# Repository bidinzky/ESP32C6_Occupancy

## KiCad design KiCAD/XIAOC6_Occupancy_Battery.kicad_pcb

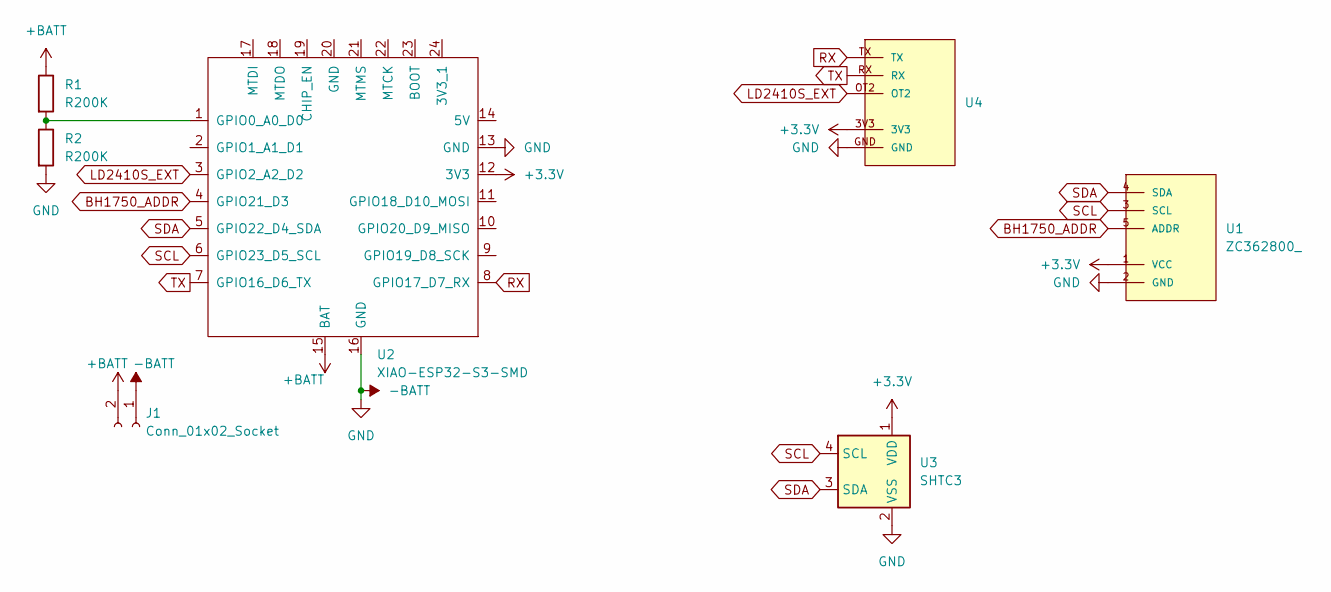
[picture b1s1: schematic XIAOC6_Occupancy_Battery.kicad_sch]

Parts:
J1: Conn_01x02_Socket; JST_PH_S2B-PH-K_1x02_P2.00mm_Horizontal
R1, R2: R200K; R_Axial_DIN0207_L6.3mm_D2.5mm_P7.62mm_Horizontal
U1: ZC362800_
U2: XIAO-ESP32-S3-SMD; XIAO-ESP32C6-DIP_1
U3: SHTC3; ASAIR_AM2302_P2.54mm_Lead2.75mm_TabDown
U4: LD2410S

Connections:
+3.3V: U1.1 (VCC), U2.12 (3V3), U3.1 (VDD), U4.3V3
+BATT: J1.2, R1.1, U2.15 (BAT)
-BATT: J1.1, R2.2, U1.2 (GND), U2.13 (GND), U2.16 (GND), U3.2 (VSS), U4.GND
BH1750_ADDR: U1.5 (ADDR), U2.4 (GPIO21_D3)
LD2410S_EXT: U2.3 (GPIO2_A2_D2), U4.OT2
unnamed: R1.2, R2.1, U2.1 (GPIO0_A0_D0)
RX: U2.8 (GPIO17_D7_RX), U4.TX
SCL: U1.3 (SCL), U2.6 (GPIO23_D5_SCL), U3.4 (SCL)
SDA: U1.4 (SDA), U2.5 (GPIO22_D4_SDA), U3.3 (SDA)
TX: U2.7 (GPIO16_D6_TX), U4.RX

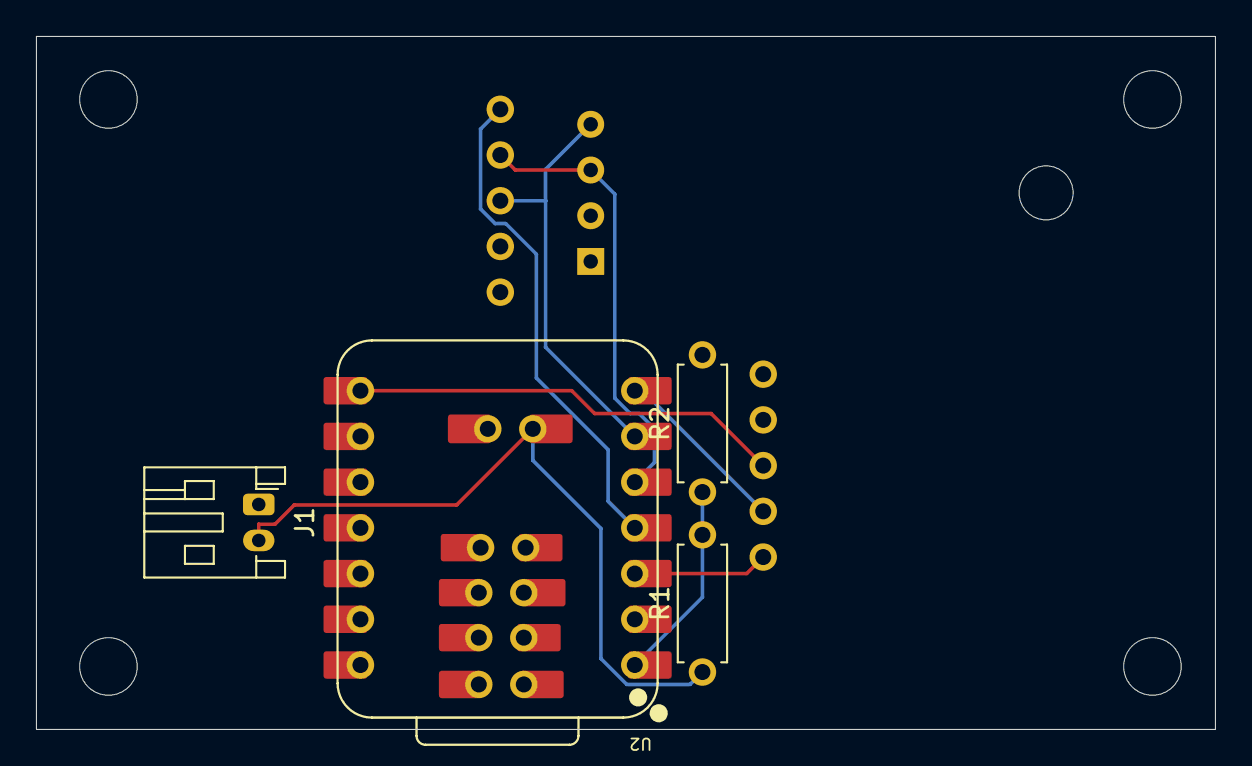
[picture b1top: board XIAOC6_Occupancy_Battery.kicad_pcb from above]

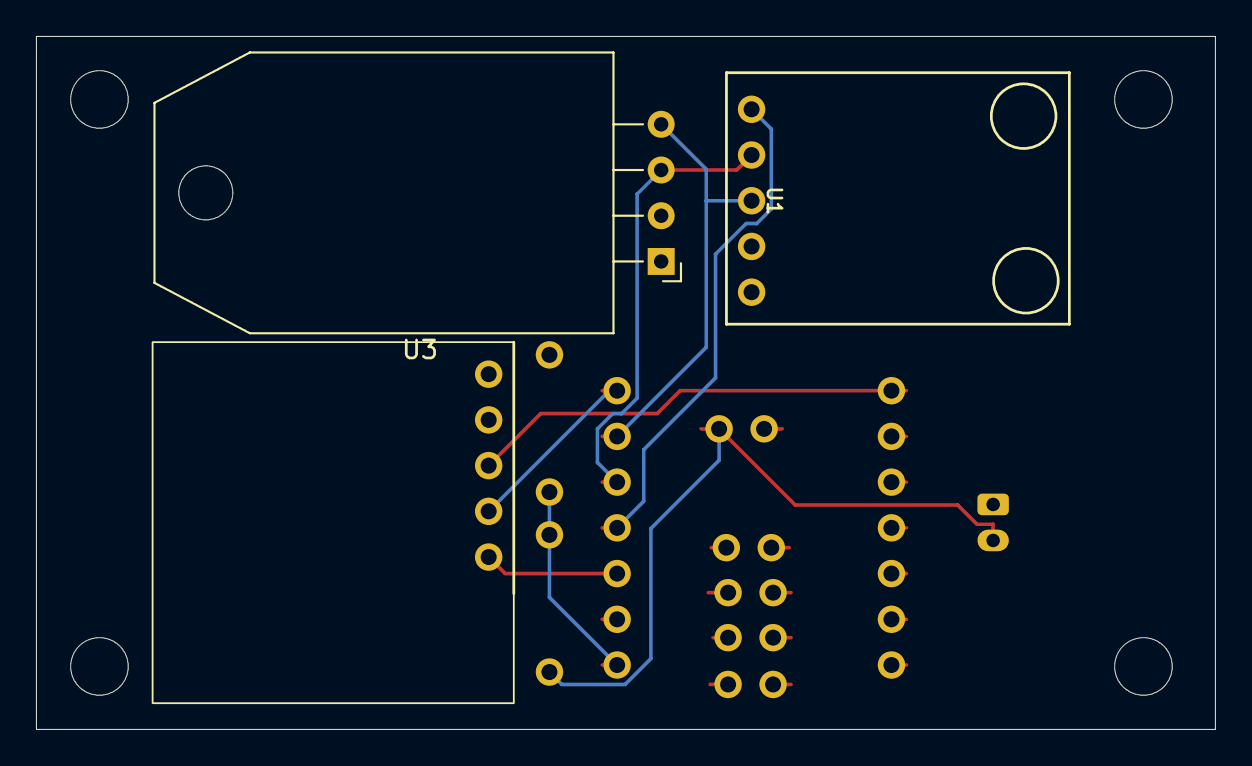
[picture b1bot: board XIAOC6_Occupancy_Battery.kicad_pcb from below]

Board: 4 copper layers, 65.5 x 38.5 mm, 11 parts (3 on the bottom side), 10 nets.

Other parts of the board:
H1, H2, H3, H4: MountingHole_3.2mm_M3_DIN965

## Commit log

2025-08-18 init
2025-08-19 add kicad pcb
